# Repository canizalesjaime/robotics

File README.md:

# Project Description 
* A compact 3D-printed mobile robot with a 4-DOF servo arm and dual TT motors for navigation.
Integrated LiDAR for obstacle avoidance, a camera with YOLOv8n for real-time object detection, and an BNO055 IMU for pose estimation.  
* A web-based interface for remote control of the robot and arm, featuring
live video with detection overlays and accelerometer data. Implemented using 
react and tailwind css to design the frontend and fast api to interact with
the backend.
* 
* [video](./robot-dashboard/public/arm_plexi_bot.mp4)

# System Design

## Software architecture
Main creates an object for each peripheral device which has a class defined: motor wheels, arm, accelerometer, camera, and lidar. Depending on feedback from frontend or physical sensors, call relevant method to determine output. One dockerfile sets up frontend for use on your computer, and
another dockerfile sets up dependencies on raspberry pi 5 to run backend.<br>

## Hardware
* stl files used for 3D printing robot base included in [freecad_files](./free_cad_files)
* pcb board power by a 7.4V LiPo battery 2200mAh, buck converter to 5V to power raspberry pi 5 and 4 servo motors, 7.4V used to power all the tt motors(with encoders)
* The robotic arm shown in was 3D printed using a model created by [FABRI_CREATOR](https://cults3d.com/en/users/FABRI_CREATOR).  
STL file available here: [Mini Robotic Arm on Cults3D](https://cults3d.com/en/3d-model/gadget/mini-robotic-arm)  
Licensed under Cults PU (Personal Use) – No commercial use or AI applications.

### Peripheral Sensors, Motor Drivers Used on Raspberry pi 5
#### IMU BNO055 
* VCC(3.3) -> PCB
* GND -> PCB
* SCL -> PCB
* SDA -> PCB

#### TB6612 Motor Driver 1
* GND -> PCB
* +12V -> PCB
* VCC(3.3) -> PCB
* ENA -> PIN 32 (GPIO 12)
* IN1 -> PIN 11 (GPIO 17)
* IN2 -> PIN 13 (GPIO 27)
* IN3 -> PIN 16 (GPIO 23)
* IN4 -> PIN 18 (GPIO 24)
* ENB -> PIN 33 (GPIO 13)
* STBY -> PIN 22 (GPIO 25) 

#### Encoder TT Motor Left
* VCC(3.3) -> PCB
* GND -> PCB
* A -> PIN 29 (GPIO 5)
* B -> PIN 31 (GPIO 6)

#### Encoder TT Motor Right
* VCC(3.3) -> PCB
* GND -> PCB
* A -> PIN 36 (GPIO 16)
* B -> PIN 37 (GPIO 26)

#### RPLidar 2D
* VCC -> PIN 4(5V)
* RX -> PIN 8 (GPIO 14)
* TX -> PIN 10(GPIO 15)
* GND -> PIN 14

#### PCB
* VCC -> PIN 1 (3.3V)
* SDA -> PIN 3 (SDA)
* SCL -> PIN 5 (SCL)
* GND -> PIN 6
* Connect lithium battery to screw terminal J1
* Connect J3 to buck converter to power Pi
* Connect J2 to get as input: 3.3V, SDA, SCL, GND 
* Connect bno055 to J5
* J7(left), and J8(right) are for encoders
* Connect tb6612 to J9, to get 3.3V(logic), 7.4V(power motors), GND  

#### PCA9685 12-bit PWM controller(removed for now)
* VCC(3.3) -> PCB
* SDA -> PCB
* SCL -> PCB
* GND -> PCB

# Working Setup
## Web App(Frontend)
* Note: Recommended to use another computer for this part to take some of the load off raspberry pi 5. Still works if you decide to use the raspberry pi 5 just a bit slower.
* works fine on ubuntu with docker setup below or on windows use devcontainers:
1. ```docker build -f ./robot_dashboard.Dockerfile -t web-setup . ```
2. ```docker run -it --rm --net=host --name web-container -v /home/jaime/homebot:/workspace web-setup:latest```

## Backend(must run on raspberry pi) 
### subscriber-publisher architecture

### transform tree

### Docker setup
1. docker build -f ./humble_pi.Dockerfile -t ros2-setup .
2. docker run -it --rm \
  --init \
  --privileged \
  --net=host \
  --device=/dev/gpiomem \
  --device=/dev/mem \
  --device=/dev/ttyAMA0 \
  --cap-add=SYS_RAWIO \
  -e DISPLAY=$DISPLAY \
  -e QT_X11_NO_MITSHM=1 \
  -v /tmp/.X11-unix:/tmp/.X11-unix:rw \
  -v /sys/class/gpio:/sys/class/gpio:cached \
  -v /dev:/dev \
  -v /run:/run \
  --name ros2-container \
  -v /home/jaime/homebot:/workspaces/homebot \
  jaimec21/jazzy_pi:latest
3. Testing backend without ros2:
```
uvicorn main:app --host 0.0.0.0 --port 8000
```

### workspace setup(backend with ros2)
1. source /opt/jazzy/setup.bash
2. cd /workspaces/homebot/ros2_ws
3. colcon build or or colcon build --symlink-install
4. source install/setup.bash
5. ros2 launch robot_control robot_move_launch.py
6. ros2 launch my_robot_description display.launch.py

### useful commands to remember
1. ros2 service call /capture_image std_srvs/srv/Trigger
2. xhost +local:root and xhost -local:root (for rviz2 on kubuntu)
3. ros2 run tf2_tools view_frames (saves tf frames in pdf)
4. ros2 pkg create my_robot_description --build-type ament_python  (create package)
5. ros2 run rqt_graph rqt_graph (view sub-pub architecture)
6. ros2 run \<package_name\> \<executable_name\>
7. ros2 launch \<package_name\> \<executable_name\>
8. simple docker:
```
docker run -it --rm --init --privileged --net=host --name ros2-container -v /home/jaime/homebot:/workspaces/homebot jaimec21/jazzy_pi:latest
```
9. open another terminal for container:
```
docker exec -it ros2-container bash
```
10. ros2 run tf2_ros static_transform_publisher \
  --x 0 --y 0 --z 0 \
  --roll 0 --pitch 0 --yaw 0 \
  --frame-id map \
  --child-frame-id laser
11. launch my_robot_description and ros2 launch rplidar_ros rplidar_c1_launch.py 

# To Do 
1. solder and plug pcb(solder shop?)
2. slam/urdf file for frames and kinematics for arm, differential-drive/odom in rviz(measure wheels in meters from centroids)(action?), test navigation with tennis
3. fix dockerfile humble_pi on on pi (image on dockerhub works fine (jazzy_pi))
4. network between computer, and homebot(ros_ip) for faster rviz. Look into networking and firewalls and other security features.
5. add camera to docker and rviz, maybe get stereo camera
6. make a better physical build, make your own arm, design pcb board no cables 
7. using pytorch course make an unsupervised grasping model, use jetson orin(check out study material on nvidia(test with olama))   
8. add flutter app

[CODE LINK](https://github.com/canizalesjaime/homebot)

## Credits
The robotic arm shown in the video above, is 3D printed using a model created by [FABRI_CREATOR](https://cults3d.com/en/users/FABRI_CREATOR).  
STL file available here: [Mini Robotic Arm on Cults3D](https://cults3d.com/en/3d-model/gadget/mini-robotic-arm)  
Licensed under Cults PU (Personal Use) – No commercial use or AI applications.

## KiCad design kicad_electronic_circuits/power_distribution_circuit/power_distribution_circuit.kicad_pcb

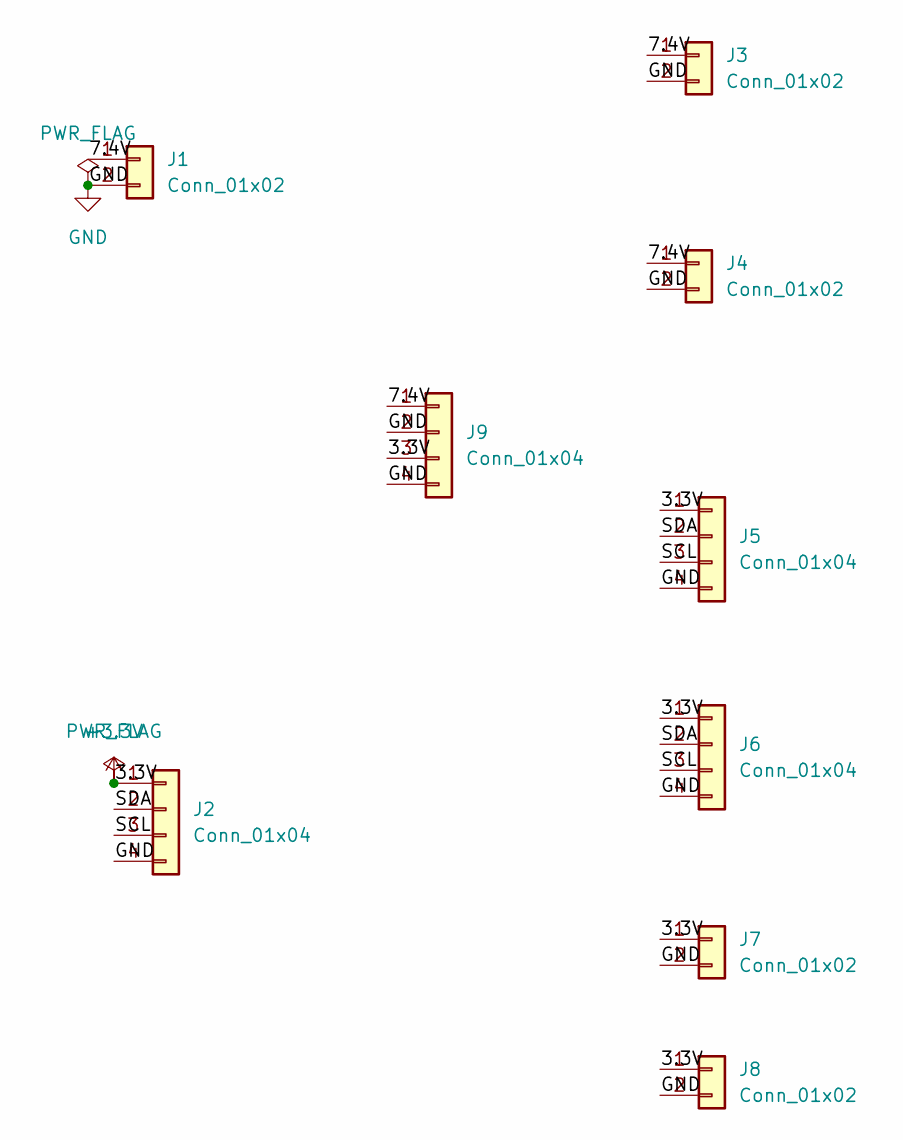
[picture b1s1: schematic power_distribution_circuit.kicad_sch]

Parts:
J1, J3, J4: Conn_01x02; Altech_AK100_1x02_P5.00mm
J2, J5, J6, J9: Conn_01x04; PinHeader_1x04_P2.54mm_Vertical
J7, J8: Conn_01x02; PinHeader_1x02_P2.54mm_Vertical

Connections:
+3.3V: J2.1, J5.1, J6.1, J7.1, J8.1, J9.3
/7.4V: J1.1, J3.1, J4.1, J9.1
/SCL: J2.3, J5.3, J6.3
/SDA: J2.2, J5.2, J6.2
GND: J1.2, J2.4, J3.2, J4.2, J5.4, J6.4, J7.2, J8.2, J9.2, J9.4

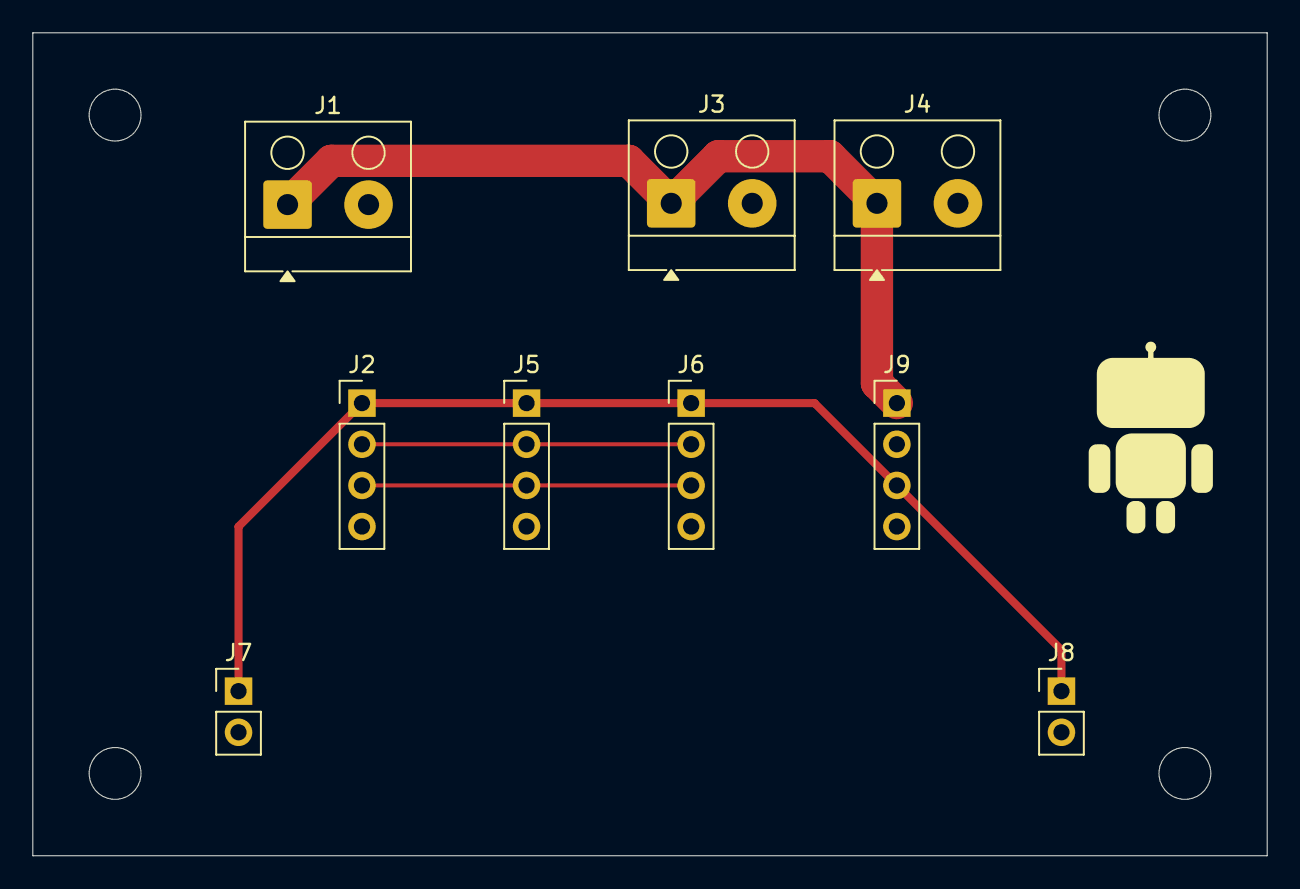
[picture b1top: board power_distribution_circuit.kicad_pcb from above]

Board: 2 copper layers, 76.2 x 50.8 mm, 9 parts (0 on the bottom side), 5 nets.

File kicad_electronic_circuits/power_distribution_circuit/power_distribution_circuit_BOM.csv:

Reference,Qty,Value,DNP,Exclude from BOM,Exclude from Board,Exclude from Simulation,Exclude from Position Files,Footprint,Datasheet,Manufacturer,MPN,Type
"J2,J5,J6,J9",4,Conn_01x04,,,,,${EXCLUDE_FROM_POS_FILES},Connector_PinHeader_2.54mm:PinHeader_1x04_P2.54mm_Vertical,,Samtec,TSW-104-14-T-S,THT
"J7,J8",2,Conn_01x02,,,,,${EXCLUDE_FROM_POS_FILES},Connector_PinHeader_2.54mm:PinHeader_1x02_P2.54mm_Vertical,,Samtec,TSW-102-14-T-S,THT
"J1,J3,J4",3,Conn_01x02,,,,,${EXCLUDE_FROM_POS_FILES},TerminalBlock_Altech:Altech_AK100_1x02_P5.00mm,https://www.mouser.com/datasheet/2/16/altech_altc_s_a0009591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,Altech,30.002,THT

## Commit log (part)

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2024-02-25 created repo
2024-03-24 added c++
2024-03-31 added some files
2024-04-26 added cleaning application
2024-04-26 added latex
2024-04-27 compiled projects
2024-09-10 added hidden textbooks
2024-10-03 fixed docker a bit
2025-01-09 prepping home_bot for ros2
2025-02-05 added cuda file
2025-02-08 some doc updates
2025-04-18 mini update
2025-04-18 minor changes from last time
2025-04-18 refactored
2025-04-18 refactor 2
2025-04-19 refernce imgs
2025-04-23 image updates
2025-04-23 some updates
2025-04-23 docker updates
2025-05-04 prepping ultrasound with motor
2025-05-05 added threading to ultra motor
2025-05-05 fixed ultra motion
2025-05-05 update readme for homebot
2025-05-05 ultrasonic volatage divider image
2025-05-13 doc updates
2025-05-14 test script
2025-05-14 added second way of moving
2025-05-14 added some images
2025-05-16 some updates to robot scripts
2026-05-14 big arm
2026-06-06 transition to ros2
2026-06-07 setup motor ros
2026-06-11 practicing with aruduino set up
2026-06-11 added freecad files
2026-06-14 fixed up documnetation a bit
2026-06-14 quick update on doc
2026-06-14 deleted gcode
2026-06-19 merging fastapi with ros2
2026-06-20 fixing up robot interface(in progress)
2026-06-21 arm mods
2026-06-21 arm mod 2
